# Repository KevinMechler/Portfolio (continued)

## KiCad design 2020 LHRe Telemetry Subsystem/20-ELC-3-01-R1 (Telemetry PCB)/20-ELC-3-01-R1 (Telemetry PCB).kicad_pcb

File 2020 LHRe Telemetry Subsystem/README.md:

# 2020 Telemetry System

In the 2020 season of Longhorn Racing Electric (LHRe), telemetry was moved from being a function of the controls subsystem to its own. This includes a new version of the telemetry PCB that I worked on last year and a newly-developed network of sensors known as SPRINKLES.

*Telemetry PCB (Cupcake)*

.jpg)

This 2-layer pcb provides a connection between the network of control boards on the vehicle and a Raspberry Pi 4 for logging CAN messages and pushing new firmware to the rest of the control boards via CAN bus. A real-time clock and GPS module also allow the Raspberry Pi to have accurate timestamps on logs and collect GPS data.

*SPRINKLES Sensor Network*

SPRINKLES started as an idea a few years ago after mechanical system leads would ask to add sensors after the controls hardware was already designed. To solve the problem of late additions to data collection and to increase the number of supported sensors, SPRINKLES was created. It was a great idea, but the team lacked the resources at the time to prioritize it or get it to work. Thus, it was first truly attempted for the 2020 season.

Each type SPRINKLES features two 6-pin connectors that carry 5V, GND, and Differential I2C. I2C on its own does poorly with long wires due to the parasitic capacitance, but the PCA9615 handles level-shifting and translates I2C to DI2C perfectly, allowing the SPRINKLES network to span across an entire electric car. To accommodate multiple I2C sensors or identical ADCs, we use the LTC4316 I2C address translator. 

.jpg)

Shown above is "Chocolate SPRINKLES" which contains a 2-channel ADC. Other versions of SPRINKLES have onboard ADCs, LDO voltage regulators, and termination resistors as needed. I should note that I led a few other students in designing the SPRINKLES PCBs, so my name is justifiably not on them.

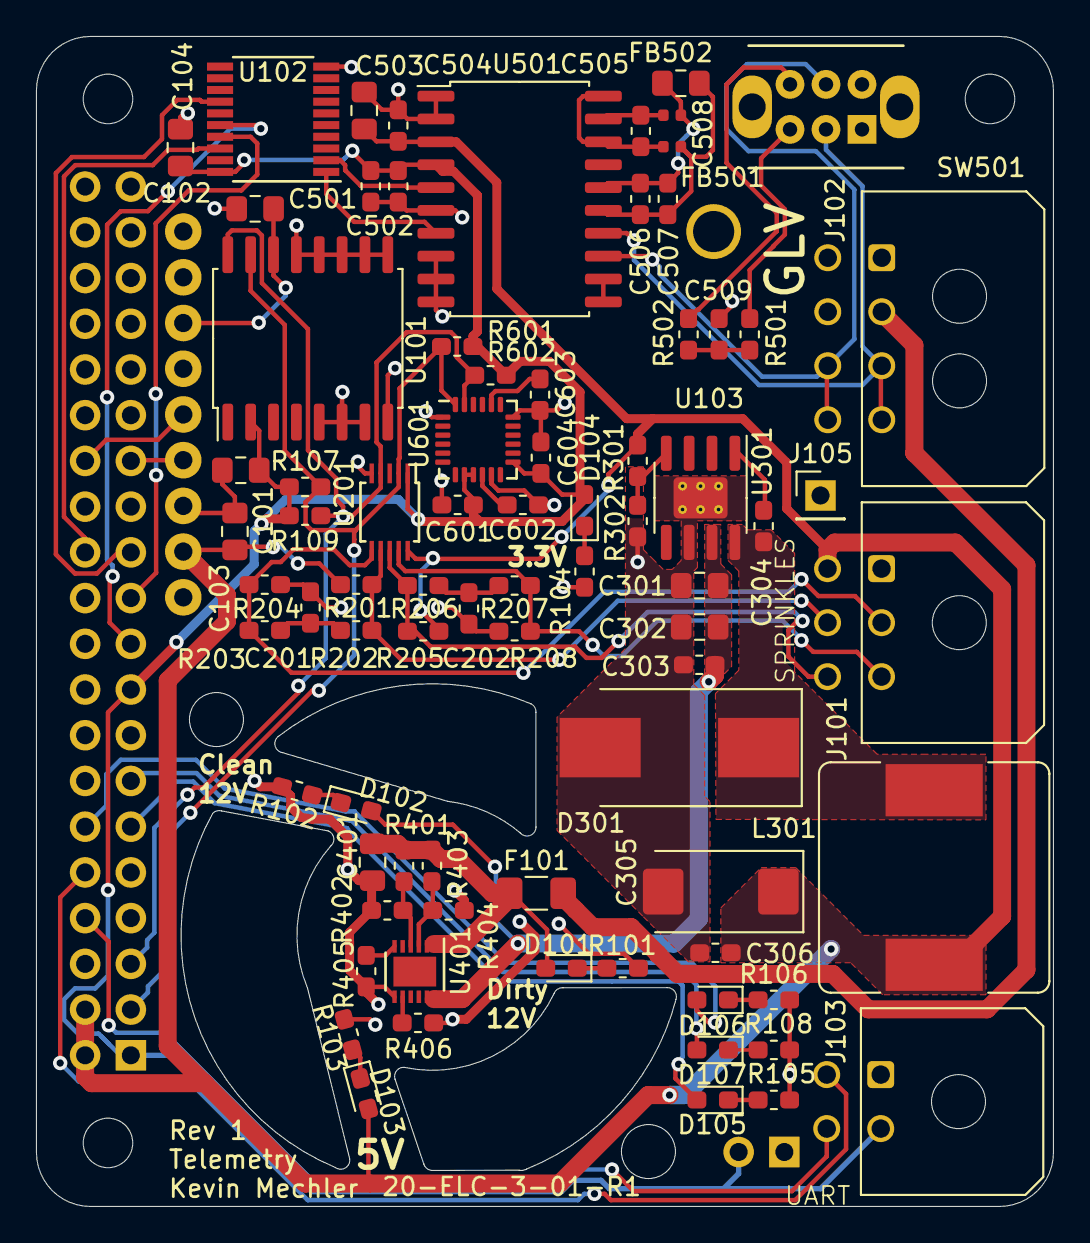
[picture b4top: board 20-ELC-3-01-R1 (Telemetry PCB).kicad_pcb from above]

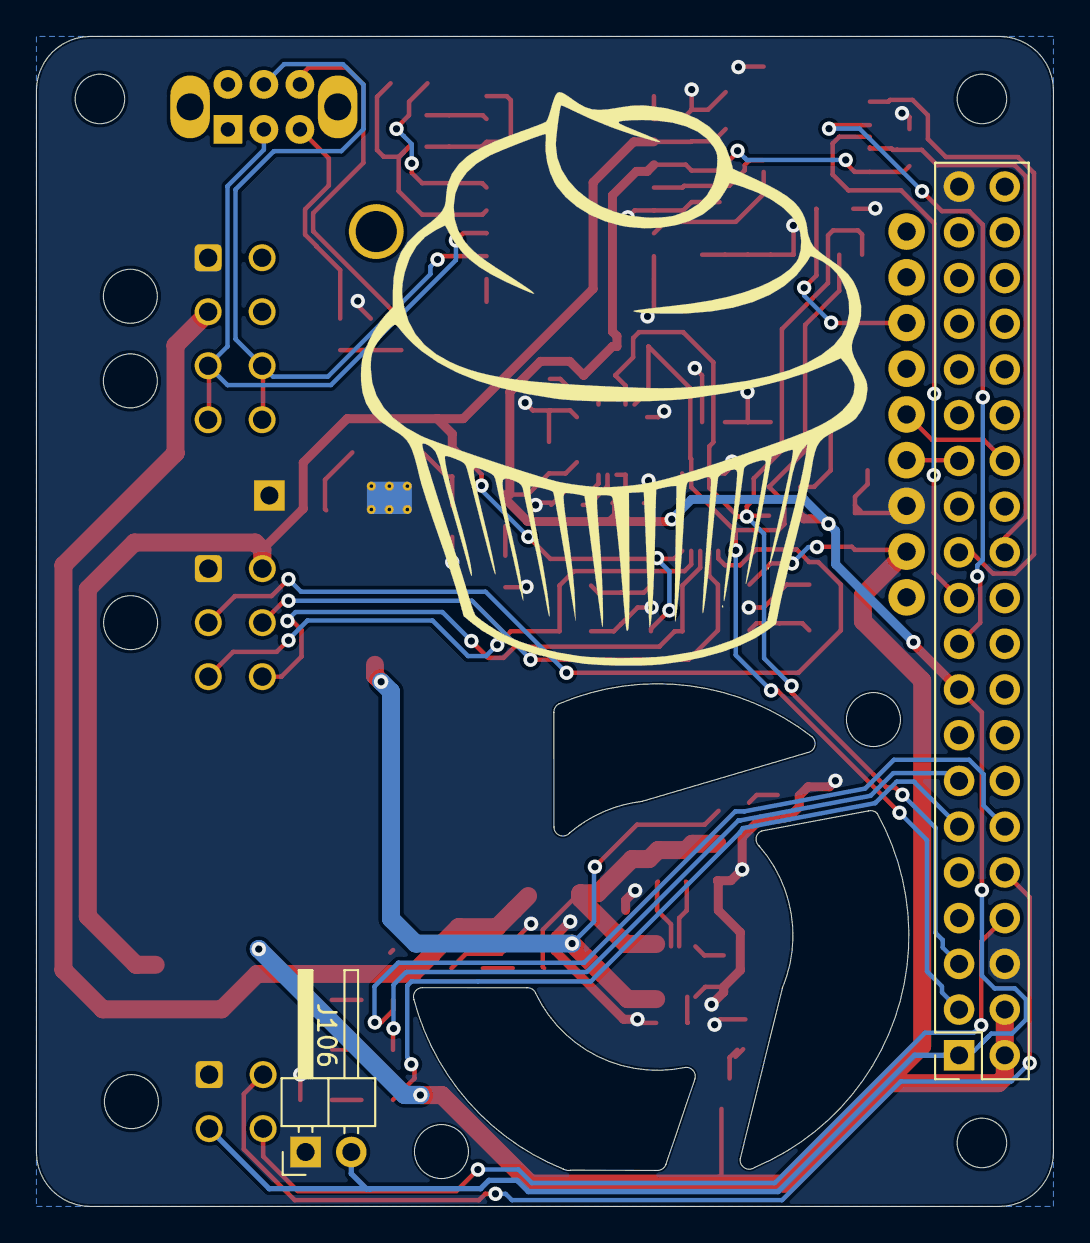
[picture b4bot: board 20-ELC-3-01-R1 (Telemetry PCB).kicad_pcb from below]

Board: 2 copper layers, 56.5 x 65.0 mm, 82 parts (2 on the bottom side), 54 nets.

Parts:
C101, C102, C104, C401: 1uF; C_0805_2012Metric_Pad1.15x1.40mm_HandSolder
C103, C503, C508: 10uF; C_0805_2012Metric_Pad1.15x1.40mm_HandSolder
C201, C202: 22nF; C_0603_1608Metric_Pad1.05x0.95mm_HandSolder
C301, C302: 4.7uF; C_0805_2012Metric_Pad1.15x1.40mm_HandSolder
C303, C304, C306, C502, C506, C601: 0.01uF; C_0603_1608Metric_Pad1.05x0.95mm_HandSolder
C305: 330uF; CP_EIA-7343-43_Kemet-X_Pad2.25x2.55mm_HandSolder
C501, C504, C507, C602, C604: 0.1uF; C_0603_1608Metric_Pad1.05x0.95mm_HandSolder
C505: 0.22uF; C_0603_1608Metric_Pad1.05x0.95mm_HandSolder
C509: 4.7nF; C_0603_1608Metric_Pad1.05x0.95mm_HandSolder
C603: 2.2nF; C_0603_1608Metric_Pad1.05x0.95mm_HandSolder
D101, D102, D103, D104, D105, D106, D107: LED; LED_0603_1608Metric_Pad1.05x0.95mm_HandSolder
D301: 40v 5A Schottky; D_SMC_Handsoldering
F101: 1A; Fuse_1206_3216Metric_Pad1.42x1.75mm_HandSolder
FB501, FB502: BKH1005LM182-T; R_0402_1005Metric
J101: SPRINKLES Harness; Molex_Micro-Fit_3.0_43045-0600_2x03_P3.00mm_Horizontal
J102: GLV Harness; Molex_Micro-Fit_3.0_43045-0800_2x04_P3.00mm_Horizontal
J103: Serial Radio; Molex_Micro-Fit_3.0_43045-0400_2x02_P3.00mm_Horizontal
J104: Raspberry_Pi_4b; Raspberry_Pi_4B_Socketed_THT_FaceDown_MountingHoles
J105: Conn_01x01; PinHeader_1x01_P2.54mm_Vertical
J106: Fan Header; PinHeader_1x02_P2.54mm_Horizontal
L301: 15uH; L_Bourns_SRR1260
R101, R102: 2k; R_0603_1608Metric_Pad1.05x0.95mm_HandSolder
R103: 680; R_0603_1608Metric_Pad1.05x0.95mm_HandSolder
R104, R105, R106, R108: 470; R_0603_1608Metric_Pad1.05x0.95mm_HandSolder
R107, R109, R301, R601, R602: 10k; R_0603_1608Metric_Pad1.05x0.95mm_HandSolder
R201, R204, R205, R208: 600; R_0603_1608Metric_Pad1.05x0.95mm_HandSolder
R202, R203, R206, R207, R501, R502: 60; R_0603_1608Metric_Pad1.05x0.95mm_HandSolder
R302: 3.16k; R_0603_1608Metric_Pad1.05x0.95mm_HandSolder
R401, R403: 2.2M; R_0603_1608Metric_Pad1.05x0.95mm_HandSolder
R402: 505k; R_0603_1608Metric_Pad1.05x0.95mm_HandSolder
R404: 226k; R_0603_1608Metric_Pad1.05x0.95mm_HandSolder
R405: 150k; R_0603_1608Metric_Pad1.05x0.95mm_HandSolder
R406: 1.5k; R_0603_1608Metric_Pad1.05x0.95mm_HandSolder
SW501: SW_DPDT; OS202011MS2QN1_DPDT_Vertical
U101: DS3231M; SOIC-16W_7.5x10.3mm_P1.27mm
U102: MCP2515-xST; TSSOP-20_4.4x6.5mm_P0.65mm
U103: Adafruit_Ultimate_GPS_V3
U201: PCA9615; TSSOP-10_3x3mm_P0.5mm
U301: TPS5450; SOIC-8-1EP_3.9x4.9mm_P1.27mm_EP2.29x3mm_ThermalVias
U401: MAX17608ATC+; DFN-12-1EP_3x3mm_P0.45mm_EP1.66x2.38mm
U501: ADM3055EBRIZ; SOIC-20W_7.5x12.8mm_P1.27mm
U601: MPU-6050; InvenSense_QFN-24_4x4mm_P0.5mm

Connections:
+3V3: C101.1, C104.1, C501.1, C502.1, C601.2, C604.2, D104.2, J103.2, J104.1, J104.17, J106.2, R107.1, R109.1, R601.1, R602.1, U101.2, U102.20, U201.1, U501.4, U601.8, U601.9, U601.13
+5V: C103.1, C305.1, C306.1, C503.2, C504.2, D103.2, J101.4, J104.2, J104.4, L301.2, R201.1, R205.1, R301.1, U103.8, U201.10, U501.3
+BATT: C102.1, U101.14, U103.3
/3.3v_SCL: J104.5, R109.2, R602.2, U101.16, U201.4, U601.23
/3.3v_SDA: J104.3, R107.2, R601.2, U101.15, U201.2, U601.24
/12V_harness: F101.2, J102.2
/CAN_High: J102.3, J102.4, SW501.2, U501.14
/CAN_Low: J102.7, J102.8, SW501.5, U501.13
/GPS_RX: J104.27, U103.6
/GPS_TX: J104.28, U103.5
/HeProtec/12V_IN: C401.1, D101.2, F101.1, R401.1, R403.1, U401.1, U401.2
/HeProtec/12V_OUT: C301.1, C302.1, C303.1, D102.2, U301.7, U401.11, U401.12
/HeProtec/CLMODE: R405.1, U401.6
/HeProtec/OVLO: R403.2, R404.1, U401.3
/HeProtec/SETI: R406.1, U401.8
/HeProtec/UVLO: R401.2, R402.1, U401.4
/Radio_RX: J103.4, J104.8
/Radio_TX: J103.3, J104.10
/SCLM: J101.2, R203.1, R204.2, U201.6
/SCLP: J101.5, R201.2, R202.1, U201.7
/SDAM: J101.3, R207.1, R208.2, U201.9
/SDAP: J101.6, R205.2, R206.1, U201.8
/isolated_can_tranceiver/can_rx: U102.2, U501.5
/isolated_can_tranceiver/can_tx: U102.1, U501.7
GND: C101.2, C102.2, C103.2, C104.2, C201.1, C202.1, C301.2, C302.2, C303.2, C305.2, C306.2, C401.2, C501.2, C502.2, C503.1, C504.1, C509.2, C601.1, C602.2, C603.2, C604.1, D301.2, J101.1, J102.1, J103.1, J104.6, J104.39, J105.1, J106.1, R101.2, R102.2, R103.2, R104.2, R105.2, R106.2, R108.2, R204.1, R208.1, R302.2, R402.2, R404.2, R405.2, R406.2, U101.5, U101.6, U101.7, U101.8, U101.9, U101.10, U101.11, U101.12, U101.13, U102.10, U103.7, U201.5, U301.6, U301.9, U401.7, U501.1, U501.2, U501.6, U501.8, U501.9, U501.10, U601.1, U601.11, U601.18
unnamed: C201.2, R202.2, R203.2
unnamed: C202.2, R206.2, R207.2
unnamed: C304.1, D301.1, L301.1, U301.8
unnamed: C304.2, U301.1
unnamed: C505.1, FB501.2, U501.18, U501.20
unnamed: C505.2, FB502.2, U501.19
unnamed: C506.1, C507.1, C508.1, FB501.1, U501.15
unnamed: C506.2, C507.2, C508.2, FB502.1, U501.16
unnamed: C509.1, R501.2, R502.2
unnamed: C602.1, U601.10
unnamed: C603.1, U601.20
unnamed: D101.1, R101.1
unnamed: D102.1, R102.1
unnamed: D103.1, R103.1
unnamed: D104.1, R104.1
unnamed: D105.1, R105.1
unnamed: D105.2, J104.11
unnamed: D106.1, R106.1
unnamed: D106.2, J104.12
unnamed: D107.1, R108.1
unnamed: D107.2, J104.13
unnamed: J104.19, U102.16
unnamed: J104.21, U102.17
unnamed: J104.23, U102.14
unnamed: J104.24, U102.18
unnamed: R301.2, R302.1, U301.4
unnamed: R501.1, SW501.3
unnamed: R502.1, SW501.6
unnamed: U501.11, U501.12

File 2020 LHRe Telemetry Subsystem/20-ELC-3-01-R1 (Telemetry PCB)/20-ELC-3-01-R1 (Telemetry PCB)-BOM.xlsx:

Longhorn Racing Electric BOM
Part Number | 19-ELC-1234
Description | Mayonnaise Dispenser
Refs | Qty | Value | Manufacturer | Part Number | Description | Footprint |  | assembled
C101,C102,C104,C401 | 4 | 1uF | ? | ? | CAP CER 1UF 25V X7R 0805 | 0805 | ? | y
C103,C503,C508 | 3 | 10uF | ? | ? | CAP CER 10UF 25V X7R 0805 | 0805 | ? | y
C201,C202 | 2 | 22nF | ? | ? | CAP CER 22nF 25V X7R 0603 | 0603 | ? | y
C301,C302 | 2 | 4.7uF | ? | ? | CAP CER 4.7UF 25V X7R 0805 | 0805 | ? | y
C303,C304,C306,C502,C506,C601 | 6 | 0.01uF | ? | ? | CAP CER 0.01UF 25V X7R 0603 | 0603 | ? | y
C305 | 1 | 330uF | Panasonic | 10TPB330M | CAP TAN 330UF 10V X7R 7343 | ? | ?
C501,C504,C507,C602,C604 | 5 | 0.1uF | ? | ? | CAP CER 0.1UF 25V X7R 0603 | 0603 | ? | y
C505 | 1 | 0.22uF | ? | ? | CAP CER 0.22UF 25V X7R 0603 | 0603 | ? | y
C509 | 1 | 4.7nF | ? | ? | CAP CER 4.7NF 25V X7R 0603 | 0603 | ? | y
C603 | 1 | 2.2nF | ? | ? | CAP CER 2.2NF 25V X7R 0603 | 0603 | ? | y
D101,D102,D103,D104 | 4 | LED | ? | ? | LED GREEN 0603 | 0603 | ? | y
D105,D106,D107 | 3 | LED | ? | ? | LED BLUE 0603 | 0603 | ? | y
D301 | 1 | 40v 5A Schottky | On Semiconductor | NRVBS540T3G | DIODE SCHOTTKY 40V 5A SMC | SMC | ?
F101 | 1 | 1A | Bel Fuse | C1Q 1 | FUSE BOARD MOUNT 1A 125VAC 63VDC | 1206 | ?
FB501,FB502 | 2 | BKH1005LM182-T | TAIYO YUDEN | BKH1005LM182-T | FERRITE BEAD 1.8 KOHM 0402 1LN | 0402 | ?
J101 | 1 | SPRINKLES Harness | Molex | 0430450601 | MICROFIT 3.0 CONN HEADER R/A DUAL GOLD 6CKT | 0430450601 | ?
J102 | 1 | GLV Harness | Molex | 0430450801 | MICROFIT 3.0 CONN HEADER R/A DUAL GOLD 8CKT | 0430450801 | ?
J103 | 1 | Serial Radio | Molex | 430450400 | MICROFIT 3.0 CONN HEADER R/A DUAL GOLD 4CKT | 430450400 | ?
J104 | 1 | Raspberry_Pi_4b | Raspberry Pi Foundation | RASPBERRY PI 4B/2GB | RASPBERRY PI 4 MODEL B 2GB SDRAM | Custom (.1" Headers) | ?
J105 | 1 | Conn_01x01 | ? | ? | PIN HEADER 1 PIN | ? | ?
J106 | 1 | Fan Header | ? | ? | ? | ? | ?
L301 | 1 | 15uH | Bourns | SRR1280A-150M | FIXED IND 15UH 5.2A 28.5 MOHM | 12mm Diode | ?
R101,R102 | 2 | 2k | ? | ? | RES SMD 2K OHM 1% 0603 | 0603 | ? | y
R103 | 1 | 680 | ? | ? | RES SMD 680 OHM 1% 0603 | 0603 | ? | y
R104,R105,R106,R108 | 4 | 470 | ? | ? | RES SMD 470 OHM 1% 0603 | 0603 | ? | y
R107,R109,R301,R601,R602 | 5 | 10k | ? | ? | RES SMD 10K OHM 1% 0603 | 0603 | ? | y
R201,R204,R205,R208 | 4 | 600 | ? | ? | RES SMD 600 OHM 1% 0603 | 0603 | ? | y - 560
R202,R203,R206,R207 | 4 | 60 | ? | ? | RES SMD 60 OHM 1% 0603 | 0603 | ? | y - 56
R302 | 1 | 3.16k | ? | ? | RES SMD 3.16K OHM 1% 0603 | 0603 | ? | y
R401,R403 | 2 | 2.2M |  |  | RES SMD 2.2M OHM 1% 0603 | 0603 | ? | y
R402 | 1 | 505k |  |  | RES SMD 505K OHM 1% 0603 | 0603 | ? | y - 510k
R404 | 1 | 226k |  |  | RES SMD 226K OHM 1% 0603 | 0603 | ?
R405 | 1 | 150k |  |  | RES SMD 150K OHM 1% 0603 | 0603 | ? | y
R406 | 1 | 1.5k |  |  | RES SMD 1.5K OHM 1% 0603 | 0603 | ? | y
R501,R502 | 2 | 60 | ? | ? | RES SMD 60 OHM 1% 0603 |  |  | y - 56
SW501 | 1 | SW_DPDT | C&K Components | OS202011MS2QN1 | Switch Slide ON ON DPDT Top Slide 0.1A 12VDC 10000Cycle PC Pins Bracket Mount/T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 | OS202011MS2QN1
U101 | 1 | DS3231M | Maxim Integrated | DS3231M+ | IC RTC CLK/CALENDAR I2C 16-SOIC | 16SOIC | ? | y
U102 | 1 | MCP2515-xST | Microchip | MCP2515-E/ST | IC CAN CONTROLLER W/SPI 20TSSOP | TSSOP20 | ?
U103 | 1 | Adafruit_Ultimate_GPS_V3 | Adafruit Industries | 746 | GPS MODULE BREAKOUT BOARD | Custom (.1" headers) | ?
U201 | 1 | PCA9615 | NXP | PCA9615DPJ | IC REDRIVER I2C 2CH 10TSSOP | TSSOP10 | ?
U301 | 1 | TPS5450 | Texas Instruments | TPS5450QDDARQ1 | IC REG BUCK ADJUSTABLE 5A 8SOPWR | 8SOIC POWERPAD | ?
U401 | 1 | MAX17608ATC+ | Maxim Integrated | MAX1760ATC+ | IC 1A OVP/OVC REV PROTECT TDFN | 12-TDFN | ?
U501 | 1 | ADM3055EBRIZ | Analog_Devices | ADM3055EBRIZ | IC TRANSCEIVER HALF 1/1 20SOIC | 20SOIC
U601 | 1 | MPU-6050 | InvenSense | MPU-6050 | IMU ACCEL/GYRO 3-AXIS I2C 24QFN | 24-QFN (4x4) | order extended part | y

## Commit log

2019-09-12 Added Telemetry PCB files
2019-09-19 Added boat
2019-09-19 Added boat images
2019-09-19 Added readme for the boat
2020-03-21 Added 2020 telemetry and keyboard projects
2020-12-30 Massive addition of content. READMEs need updating
    Added project folders for the keyboard case, shifter mount, as well as high school robotics. The content needs to be revised, and the READMEs need to be properly written.
2020-12-30 Updated Racing Sim Resources
2021-01-17 Added screencaps of prototyping parts
